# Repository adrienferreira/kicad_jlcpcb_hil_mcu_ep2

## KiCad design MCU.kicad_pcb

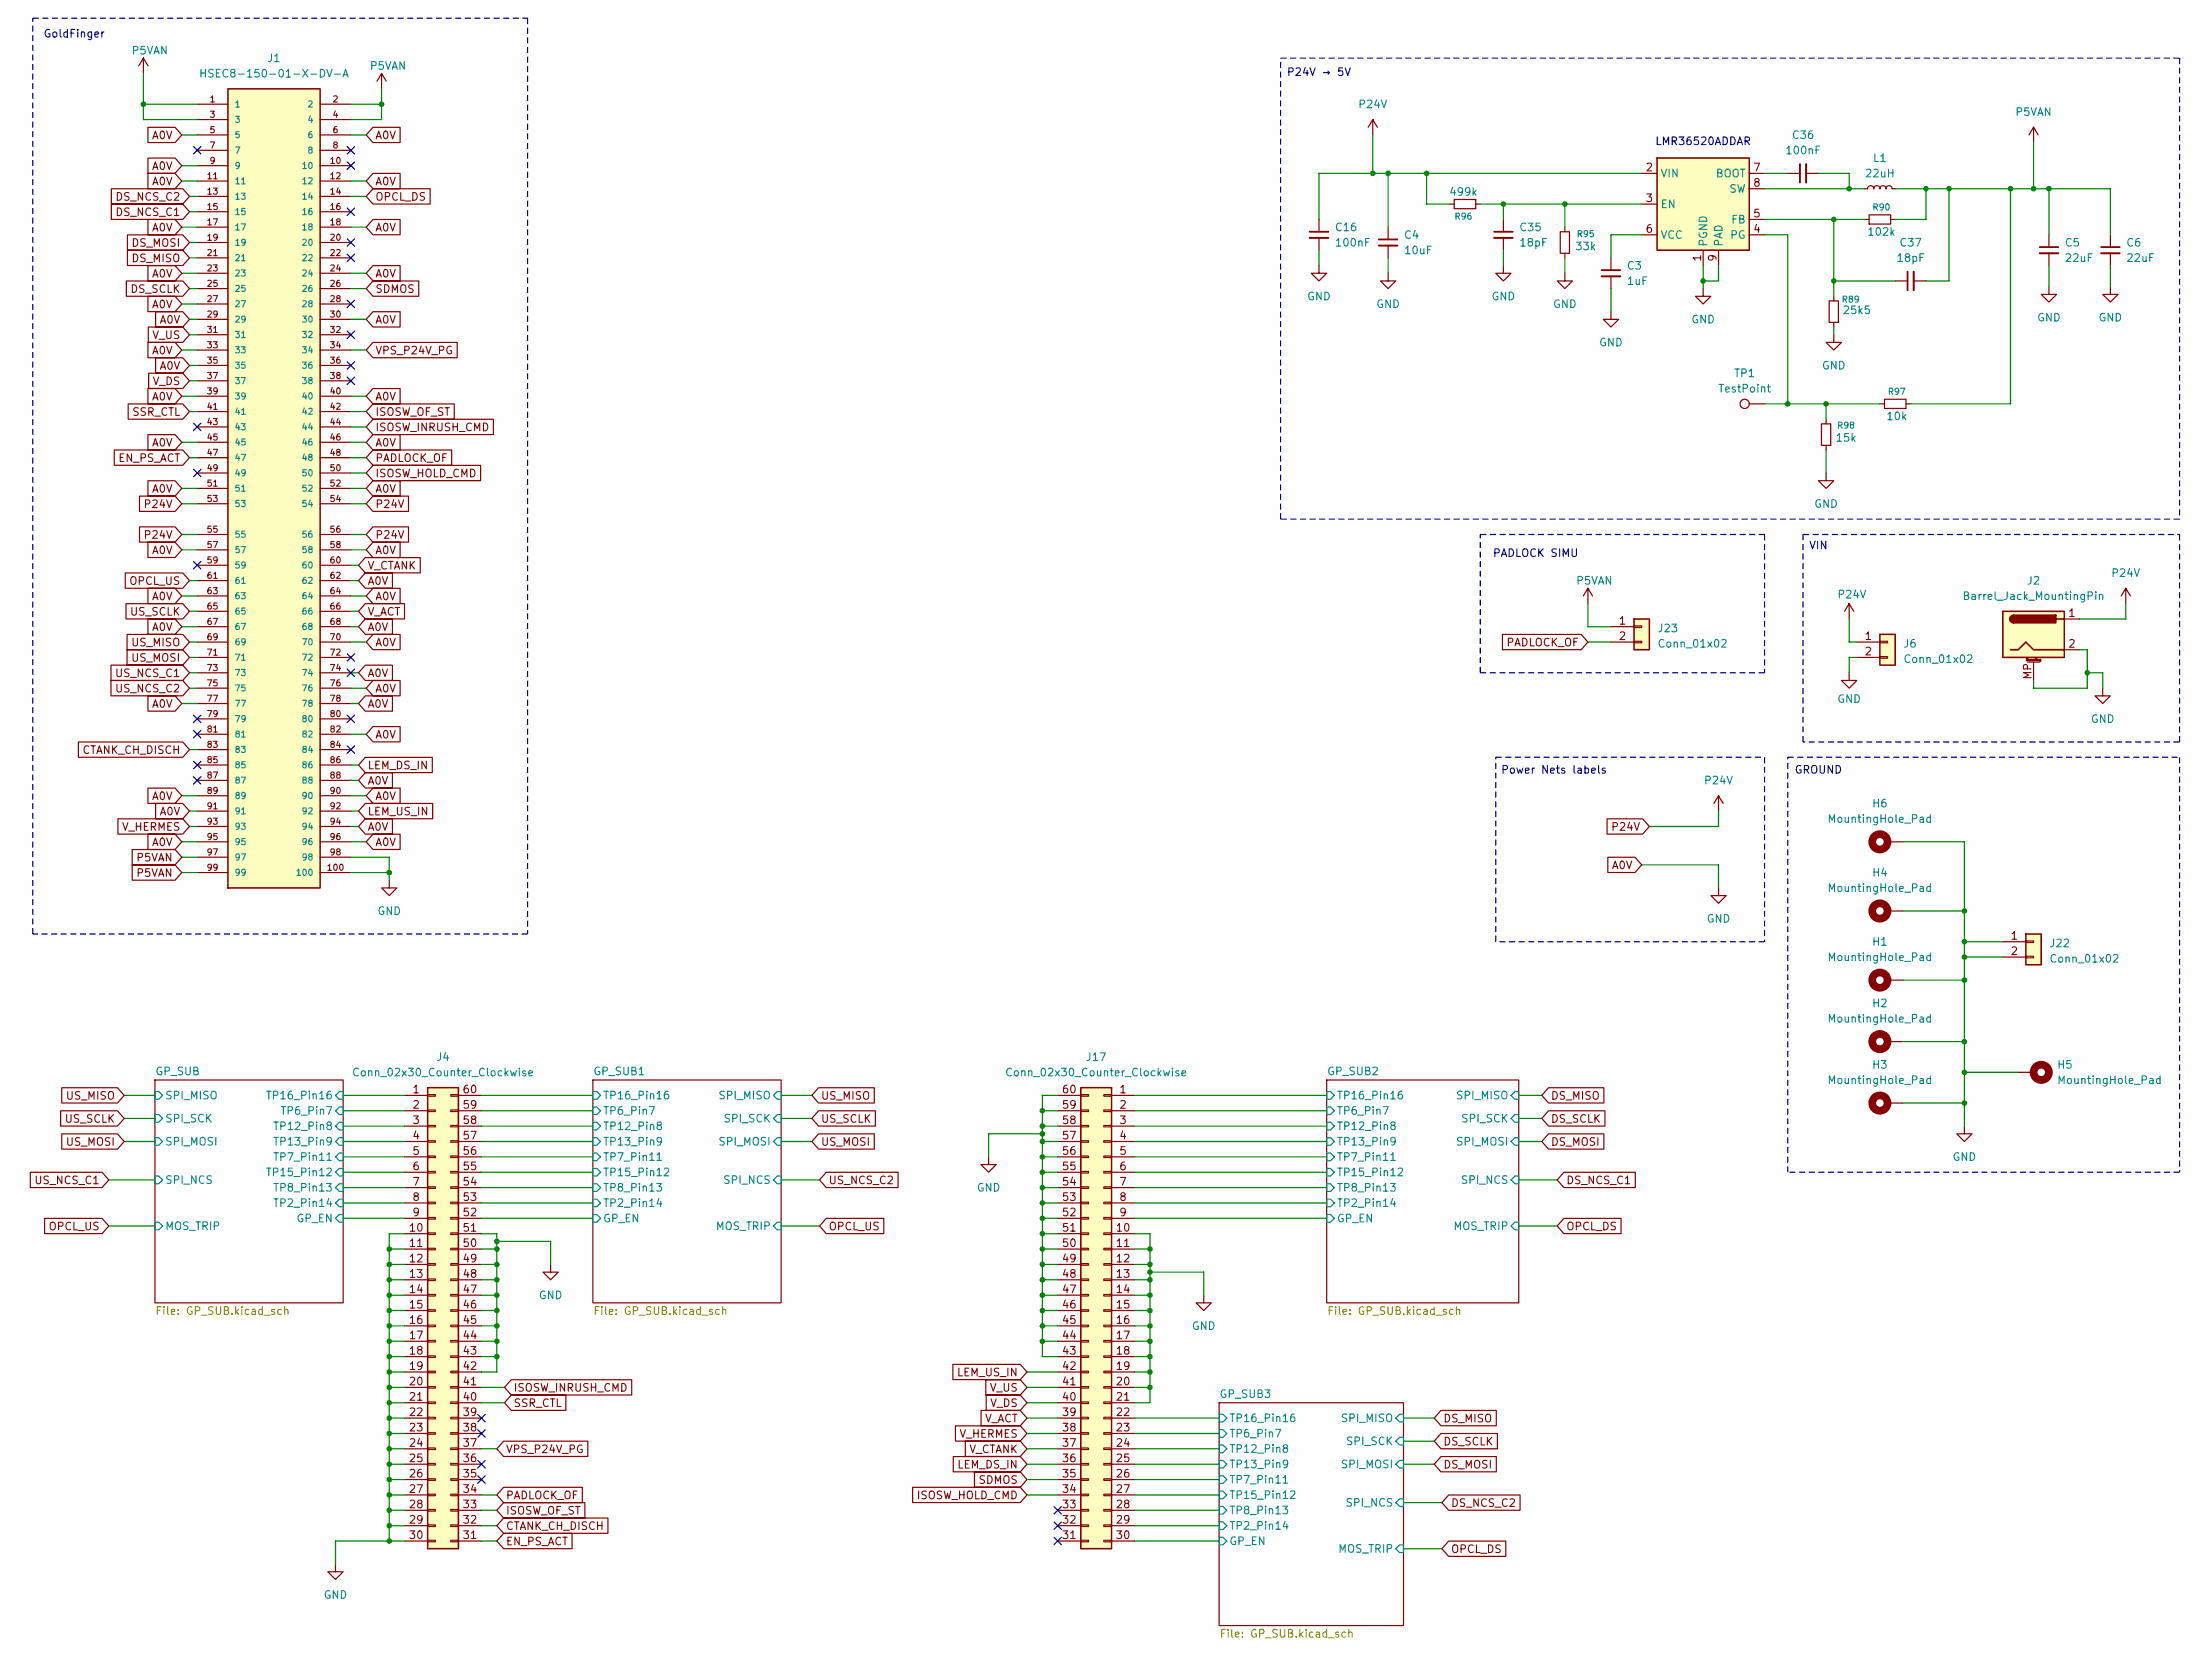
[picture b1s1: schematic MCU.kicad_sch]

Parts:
C3: 1uF; C_0603_1608Metric
C4: 10uF; C_0805_2012Metric
C5, C6: 22uF; C_0603_1608Metric
C16: 100nF; C_0603_1608Metric; JLCPCB Part# C1525
C35: 18pF; C_0402_1005Metric; JLCPCB Part # C23733
C36: 100nF; C_0603_1608Metric
C37: 18pF; C_0603_1608Metric; JLCPCB Part # C23733
H1, H2, H3, H4, H5, H6: MountingHole_Pad; MountingHole_2.2mm_M2_DIN965_Pad
J1: HSEC8-150-01-X-DV-A; Samtec_HSEC8-150-01-X-DV-A_2x50_P0.8mm_Pol27_Socket_Alignme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; PARTREV AH
J2: Barrel_Jack_MountingPin; BarrelJack_CUI_PJ-063AH_Horizontal
J4, J17: Conn_02x30_Counter_Clockwise; PinHeader_2x30_P2.54mm_Vertical
J6, J22, J23: Conn_01x02; PinHeader_1x02_P2.54mm_Vertical; JLCPCB Part# C492401
L1: 22uH; L_TDK_SLF10145
R89: 25k5; R_0603_1608Metric
R90: 102k; R_0603_1608Metric
R95: 33k; R_0603_1608Metric
R96: 499k; R_0603_1608Metric
R97: 10k; R_0603_1608Metric
R98: 15k; R_0603_1608Metric
TP1: TestPoint; TestPoint_Pad_1.5x1.5mm
U3: LMR36510ADDA; Texas_HTSOP-8-1EP_3.9x4.9mm_P1.27mm_EP2.95x4.9mm_Mask2.4x3.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

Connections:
/GP_SUB1/GP_EN: J4.52; also elsewhere on the board
/GP_SUB1/P7_VIMOSA1: J4.59; also elsewhere on the board
/GP_SUB1/P8_VIMOSA2: J4.58; also elsewhere on the board
/GP_SUB1/P9_VTMP: J4.57; also elsewhere on the board
/GP_SUB1/P11_EN_PSD: J4.56; also elsewhere on the board
/GP_SUB1/P12_GP_OPCL_T2: J4.55; also elsewhere on the board
/GP_SUB1/P13_GP_OPCL_T1: J4.54; also elsewhere on the board
/GP_SUB1/TP2_Pin14: J4.53; also elsewhere on the board
/GP_SUB1/TP16_Pin16: J4.60; also elsewhere on the board
/GP_SUB2/GP_EN: J17.9; also elsewhere on the board
/GP_SUB2/P7_VIMOSA1: J17.2; also elsewhere on the board
/GP_SUB2/P8_VIMOSA2: J17.3; also elsewhere on the board
/GP_SUB2/P9_VTMP: J17.4; also elsewhere on the board
/GP_SUB2/P11_EN_PSD: J17.5; also elsewhere on the board
/GP_SUB2/P12_GP_OPCL_T2: J17.6; also elsewhere on the board
/GP_SUB2/P13_GP_OPCL_T1: J17.7; also elsewhere on the board
/GP_SUB2/TP2_Pin14: J17.8; also elsewhere on the board
/GP_SUB2/TP16_Pin16: J17.1; also elsewhere on the board
/GP_SUB3/GP_EN: J17.30; also elsewhere on the board
/GP_SUB3/P7_VIMOSA1: J17.23; also elsewhere on the board
/GP_SUB3/P8_VIMOSA2: J17.24; also elsewhere on the board
/GP_SUB3/P9_VTMP: J17.25; also elsewhere on the board
/GP_SUB3/P11_EN_PSD: J17.26; also elsewhere on the board
/GP_SUB3/P12_GP_OPCL_T2: J17.27; also elsewhere on the board
/GP_SUB3/P13_GP_OPCL_T1: J17.28; also elsewhere on the board
/GP_SUB3/TP2_Pin14: J17.29; also elsewhere on the board
/GP_SUB3/TP16_Pin16: J17.22; also elsewhere on the board
/GP_SUB/GP_EN: J4.9; also elsewhere on the board
/GP_SUB/P7_VIMOSA1: J4.2; also elsewhere on the board
/GP_SUB/P8_VIMOSA2: J4.3; also elsewhere on the board
/GP_SUB/P9_VTMP: J4.4; also elsewhere on the board
/GP_SUB/P11_EN_PSD: J4.5; also elsewhere on the board
/GP_SUB/P12_GP_OPCL_T2: J4.6; also elsewhere on the board
/GP_SUB/P13_GP_OPCL_T1: J4.7; also elsewhere on the board
/GP_SUB/TP2_Pin14: J4.8; also elsewhere on the board
/GP_SUB/TP16_Pin16: J4.1; also elsewhere on the board
A0V: C3.2, C4.2, C5.2, C6.2, C16.2, C35.2, H1.1 (1_1), H2.1 (1_1), H3.1 (1_1), H4.1 (1_1), H5.1 (1_1), H6.1 (1_1), J1.5, J1.6, J1.9, J1.11, J1.12, J1.17, J1.18, J1.23, J1.24, J1.27, J1.29, J1.30, J1.33, J1.35, J1.39, J1.40, J1.45, J1.46, J1.51, J1.52, J1.57, J1.58, J1.62, J1.63, J1.64, J1.67, J1.68, J1.70, J1.74, J1.76, J1.77, J1.78, J1.82, J1.88, J1.89, J1.90, J1.91, J1.94, J1.95, J1.96, J1.98, J1.100, J2.2, J2.MP (MountPin_MP), J4.10, J4.11, J4.12, J4.13, J4.14, J4.15, J4.16, J4.17, J4.18, J4.19, J4.20, J4.21, J4.22, J4.23, J4.24, J4.25, J4.26, J4.27, J4.28, J4.29, J4.30, J4.42, J4.43, J4.44, J4.45, J4.46, J4.47, J4.48, J4.49, J4.50, J4.51, J6.2, J17.10, J17.11, J17.12, J17.13, J17.14, J17.15, J17.16, J17.17, J17.18, J17.19, J17.20, J17.21, J17.43, J17.44, J17.45, J17.46, J17.47, J17.48, J17.49, J17.50, J17.51, J17.52, J17.53, J17.54, J17.55, J17.56, J17.57, J17.58, J17.59, J17.60, J22.1, J22.2, R89.1, R95.1, R98.1, U3.1 (PGND), U3.9 (PAD); also elsewhere on the board
CTANK_CH_DISCH: J1.83, J4.32
DS_MISO: J1.21; also elsewhere on the board
DS_MOSI: J1.19; also elsewhere on the board
DS_NCS_C1: J1.15; also elsewhere on the board
DS_NCS_C2: J1.13; also elsewhere on the board
DS_SCLK: J1.25; also elsewhere on the board
EN_PS_ACT: J1.47, J4.31
ISOSW_HOLD_CMD: J1.50, J17.34
ISOSW_INRUSH_CMD: J1.44, J4.41
ISOSW_OF_ST: J1.42, J4.33
LEM_DS_IN: J1.86, J17.36
LEM_US_IN: J1.92, J17.42
unnamed: C36.1, U3.7 (BOOT)
unnamed: C35.1, R95.2, R96.1, U3.3 (EN)
unnamed: C37.1, R89.2, R90.1, U3.5 (FB)
unnamed: R97.1, R98.2, TP1.1 (1_1), U3.4 (PG)
unnamed: C36.2, L1.1, U3.8 (SW)
unnamed: C3.1, U3.6 (VCC)
OPCL_DS: J1.14; also elsewhere on the board
OPCL_US: J1.61; also elsewhere on the board
P5VAN: C5.1, C6.1, C37.2, J1.1, J1.2, J1.3, J1.4, J1.97, J1.99, J23.1, L1.2, R90.2, R97.2; also elsewhere on the board
P24V: C4.1, C16.1, J1.53, J1.54, J1.55, J1.56, J2.1, J6.1, R96.2, U3.2 (VIN)
PADLOCK_OF: J1.48, J4.34, J23.2
SDMOS: J1.26, J17.35
SSR_CTL: J1.41, J4.40
US_MISO: J1.69; also elsewhere on the board
US_MOSI: J1.71; also elsewhere on the board
US_NCS_C1: J1.73; also elsewhere on the board
US_NCS_C2: J1.75; also elsewhere on the board
US_SCLK: J1.65; also elsewhere on the board
VPS_P24V_PG: J1.34, J4.37
V_ACT: J1.66, J17.39
V_CTANK: J1.60, J17.37
V_DS: J1.37, J17.40
V_HERMES: J1.93, J17.38
V_US: J1.31, J17.41

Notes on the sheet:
P24V → 5V
GoldFinger
Power Nets labels
GROUND
LMR36520ADDAR
PADLOCK SIMU
VIN

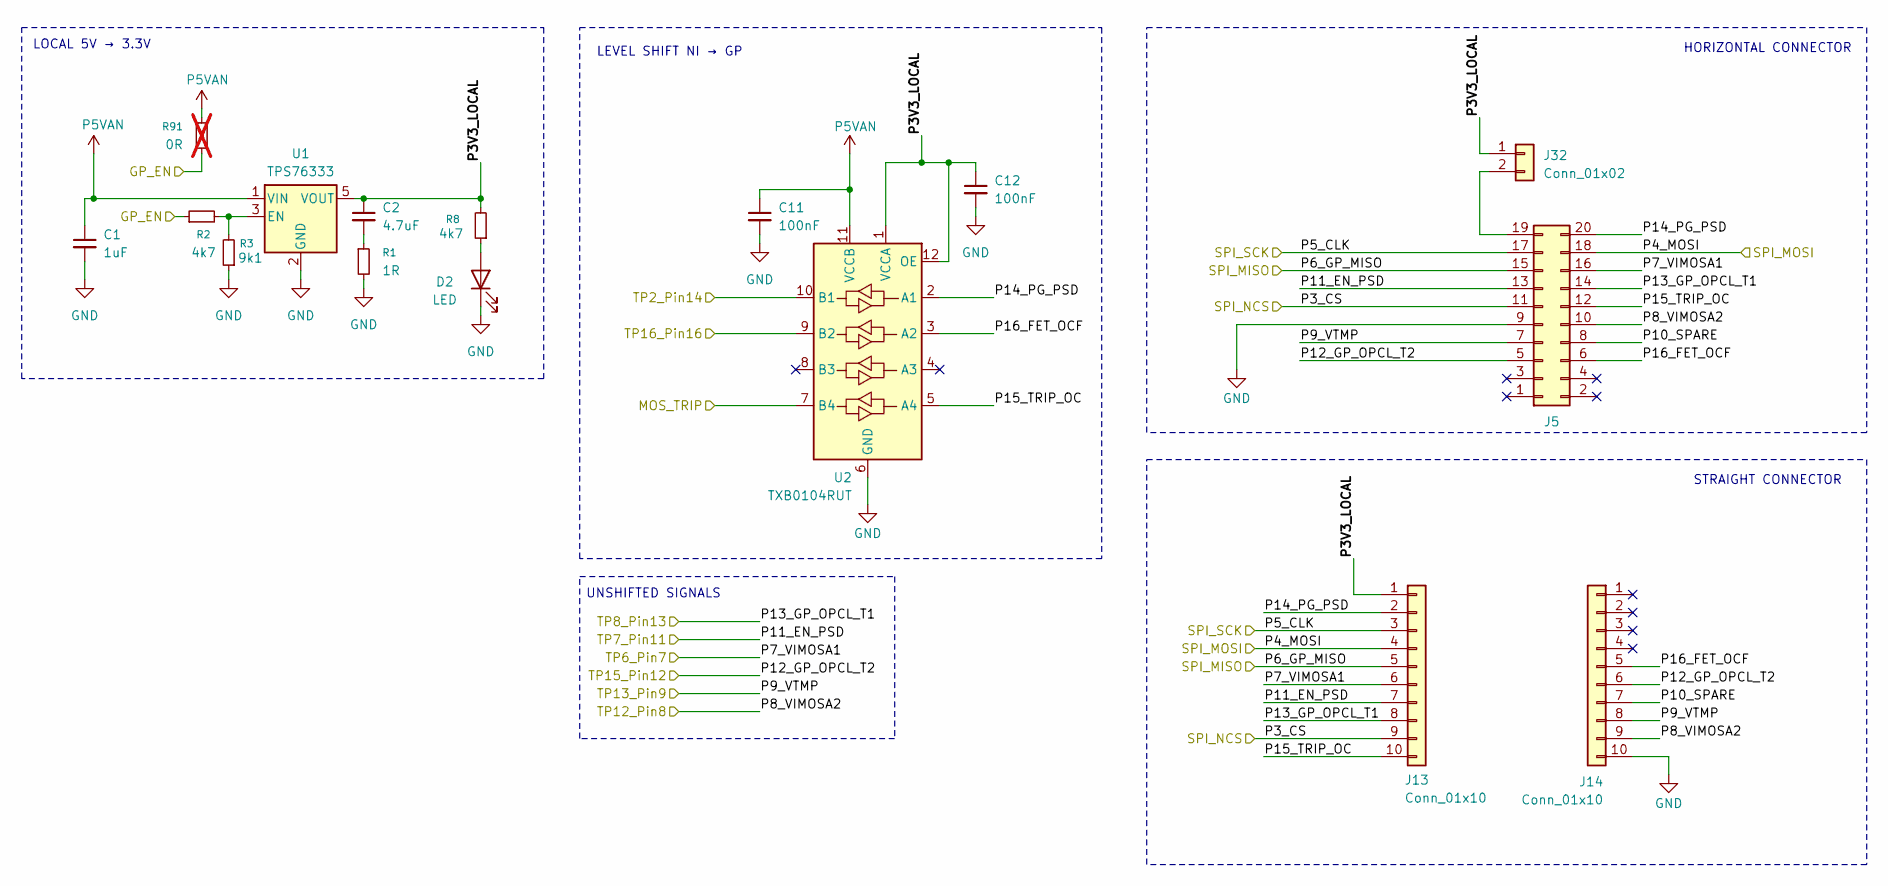
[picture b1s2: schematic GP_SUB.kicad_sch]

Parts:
C1: 1uF; C_0603_1608Metric
C2: 4.7uF; C_0603_1608Metric
C11, C12: 100nF; C_0402_1005Metric; JLCPCB Part# C1525
D2: LED; LED_0805_2012Metric; JLCPCB Part# C25170728
J5: Conn_02x10_Odd_Even; PinHeader_2x10_P2.54mm_Vertical; JLCPCB Part# C706900
J13, J14: Conn_01x10; PinSocket_1x10_P2.54mm_Vertical
J32: Conn_01x02; PinHeader_1x02_P2.54mm_Vertical; JLCPCB Part# C492401
R1: 1R; R_0603_1608Metric
R2: 4k7; R_0603_1608Metric
R3: 9k1; R_0603_1608Metric
R8: 4k7; R_0603_1608Metric; JLCPCB Part# C23138
R91: 0R; R_0603_1608Metric; not fitted
U1: TPS76333; SOT-23-5
U2: TXB0104RUT; Texas_R-PUQFN-N12

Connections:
/GP_SUB/GP_EN: R2.1, R91.2; also elsewhere on the board
/GP_SUB/P3V3_LOCAL: C2.1, C12.1, J13.1, J32.1, R8.2, U1.5 (VOUT), U2.1 (VCCA), U2.12 (OE)
/GP_SUB/P7_VIMOSA1: J5.16, J13.6; also elsewhere on the board
/GP_SUB/P8_VIMOSA2: J5.10, J14.9; also elsewhere on the board
/GP_SUB/P9_VTMP: J5.7, J14.8; also elsewhere on the board
/GP_SUB/P10_SPARE: J5.8, J14.7
/GP_SUB/P11_EN_PSD: J5.13, J13.7; also elsewhere on the board
/GP_SUB/P12_GP_OPCL_T2: J5.5, J14.6; also elsewhere on the board
/GP_SUB/P13_GP_OPCL_T1: J5.14, J13.8; also elsewhere on the board
/GP_SUB/P14_PG_PSD: J5.20, J13.2, U2.2 (A1)
/GP_SUB/P15_TRIP_OC: J5.12, J13.10, U2.5 (A4)
/GP_SUB/P16_FET_OCF: J5.6, J14.5, U2.3 (A2)
/GP_SUB/TP2_Pin14: U2.10 (B1); also elsewhere on the board
/GP_SUB/TP16_Pin16: U2.9 (B2); also elsewhere on the board
A0V: C1.2, C11.2, C12.2, D2.1 (K), J5.9, J14.10, R1.2, R3.1, U1.2 (GND), U2.6 (GND); also elsewhere on the board
unnamed: C2.2, R1.1
unnamed: D2.2 (A), R8.1
unnamed: J5.19, J32.2
unnamed: R2.2, R3.2, U1.3 (EN)
OPCL_US: U2.7 (B4); also elsewhere on the board
P5VAN: C1.1, C11.1, R91.1, U1.1 (VIN), U2.11 (VCCB); also elsewhere on the board
US_MISO: J5.15, J13.5; also elsewhere on the board
US_MOSI: J5.18, J13.4; also elsewhere on the board
US_NCS_C1: J5.11, J13.9; also elsewhere on the board
US_SCLK: J5.17, J13.3; also elsewhere on the board

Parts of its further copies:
C15, C19, C23, C25, C29, C31: 100nF; C_0402_1005Metric; JLCPCB Part# C1525
C21, C27, C33: 1uF; C_0603_1608Metric
C22, C28, C34: 4.7uF; C_0603_1608Metric
D4, D5, D6: LED; LED_0805_2012Metric; JLCPCB Part# C25170728
J7, J8, J11, J12, J18, J19: Conn_01x10; PinSocket_1x10_P2.54mm_Vertical
J9, J15, J20: Conn_01x02; PinHeader_1x02_P2.54mm_Vertical; JLCPCB Part# C492401
J10, J16, J21: Conn_02x10_Odd_Even; PinHeader_2x10_P2.54mm_Vertical; JLCPCB Part# C706900
R29, R93, R94: 0R; R_0603_1608Metric; not fitted
R30, R57, R77: 4k7; R_0603_1608Metric
R31, R58, R78: 9k1; R_0603_1608Metric
R32, R59, R79: 1R; R_0603_1608Metric
R68, R88, R92: 4k7; R_0603_1608Metric; JLCPCB Part# C23138
U6, U9, U12: TXB0104RUT; Texas_R-PUQFN-N12
U8, U11, U14: TPS76333; SOT-23-5

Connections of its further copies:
/GP_SUB1/GP_EN: R29.2, R30.1; also elsewhere on the board
/GP_SUB1/P3V3_LOCAL: C19.1, C22.1, J7.1, J9.1, R92.2, U6.1 (VCCA), U6.12 (OE), U8.5 (VOUT)
/GP_SUB1/P7_VIMOSA1: J7.6, J10.16; also elsewhere on the board
/GP_SUB1/P8_VIMOSA2: J8.9, J10.10; also elsewhere on the board
/GP_SUB1/P9_VTMP: J8.8, J10.7; also elsewhere on the board
/GP_SUB1/P10_SPARE: J8.7, J10.8
/GP_SUB1/P11_EN_PSD: J7.7, J10.13; also elsewhere on the board
/GP_SUB1/P12_GP_OPCL_T2: J8.6, J10.5; also elsewhere on the board
/GP_SUB1/P13_GP_OPCL_T1: J7.8, J10.14; also elsewhere on the board
/GP_SUB1/P14_PG_PSD: J7.2, J10.20, U6.2 (A1)
/GP_SUB1/P15_TRIP_OC: J7.10, J10.12, U6.5 (A4)
/GP_SUB1/P16_FET_OCF: J8.5, J10.6, U6.3 (A2)
/GP_SUB1/TP2_Pin14: U6.10 (B1); also elsewhere on the board
/GP_SUB1/TP16_Pin16: U6.9 (B2); also elsewhere on the board
/GP_SUB2/GP_EN: R57.1, R93.2; also elsewhere on the board
/GP_SUB2/P3V3_LOCAL: C25.1, C28.1, J11.1, J15.1, R68.2, U9.1 (VCCA), U9.12 (OE), U11.5 (VOUT)
/GP_SUB2/P7_VIMOSA1: J11.6, J16.16; also elsewhere on the board
/GP_SUB2/P8_VIMOSA2: J12.9, J16.10; also elsewhere on the board
/GP_SUB2/P9_VTMP: J12.8, J16.7; also elsewhere on the board
/GP_SUB2/P10_SPARE: J12.7, J16.8
/GP_SUB2/P11_EN_PSD: J11.7, J16.13; also elsewhere on the board
/GP_SUB2/P12_GP_OPCL_T2: J12.6, J16.5; also elsewhere on the board
/GP_SUB2/P13_GP_OPCL_T1: J11.8, J16.14; also elsewhere on the board
/GP_SUB2/P14_PG_PSD: J11.2, J16.20, U9.2 (A1)
/GP_SUB2/P15_TRIP_OC: J11.10, J16.12, U9.5 (A4)
/GP_SUB2/P16_FET_OCF: J12.5, J16.6, U9.3 (A2)
/GP_SUB2/TP2_Pin14: U9.10 (B1); also elsewhere on the board
/GP_SUB2/TP16_Pin16: U9.9 (B2); also elsewhere on the board
/GP_SUB3/GP_EN: R77.1, R94.2; also elsewhere on the board
/GP_SUB3/P3V3_LOCAL: C31.1, C34.1, J18.1, J20.1, R88.2, U12.1 (VCCA), U12.12 (OE), U14.5 (VOUT)
/GP_SUB3/P7_VIMOSA1: J18.6, J21.16; also elsewhere on the board
/GP_SUB3/P8_VIMOSA2: J19.9, J21.10; also elsewhere on the board
/GP_SUB3/P9_VTMP: J19.8, J21.7; also elsewhere on the board
/GP_SUB3/P10_SPARE: J19.7, J21.8
/GP_SUB3/P11_EN_PSD: J18.7, J21.13; also elsewhere on the board
/GP_SUB3/P12_GP_OPCL_T2: J19.6, J21.5; also elsewhere on the board
/GP_SUB3/P13_GP_OPCL_T1: J18.8, J21.14; also elsewhere on the board
/GP_SUB3/P14_PG_PSD: J18.2, J21.20, U12.2 (A1)
/GP_SUB3/P15_TRIP_OC: J18.10, J21.12, U12.5 (A4)
/GP_SUB3/P16_FET_OCF: J19.5, J21.6, U12.3 (A2)
/GP_SUB3/TP2_Pin14: U12.10 (B1); also elsewhere on the board
/GP_SUB3/TP16_Pin16: U12.9 (B2); also elsewhere on the board
A0V: C15.2, C19.2, C21.2, C23.2, C25.2, C27.2, C29.2, C31.2, C33.2, D4.1 (K), D5.1 (K), D6.1 (K), J8.10, J10.9, J12.10, J16.9, J19.10, J21.9, R31.1, R32.2, R58.1, R59.2, R78.1, R79.2, U6.6 (GND), U8.2 (GND), U9.6 (GND), U11.2 (GND), U12.6 (GND), U14.2 (GND); also elsewhere on the board
DS_MISO: J11.5, J16.15, J18.5, J21.15; also elsewhere on the board
DS_MOSI: J11.4, J16.18, J18.4, J21.18; also elsewhere on the board
DS_NCS_C1: J11.9, J16.11; also elsewhere on the board
DS_NCS_C2: J18.9, J21.11; also elsewhere on the board
DS_SCLK: J11.3, J16.17, J18.3, J21.17; also elsewhere on the board
unnamed: C22.2, R32.1
unnamed: C28.2, R59.1
unnamed: C34.2, R79.1
unnamed: D4.2 (A), R92.1
unnamed: D5.2 (A), R68.1
unnamed: D6.2 (A), R88.1
unnamed: J9.2, J10.19
unnamed: J15.2, J16.19
unnamed: J20.2, J21.19
unnamed: R30.2, R31.2, U8.3 (EN)
unnamed: R57.2, R58.2, U11.3 (EN)
unnamed: R77.2, R78.2, U14.3 (EN)
OPCL_DS: U9.7 (B4), U12.7 (B4); also elsewhere on the board
OPCL_US: U6.7 (B4); also elsewhere on the board
P5VAN: C15.1, C21.1, C23.1, C27.1, C29.1, C33.1, R29.1, R93.1, R94.1, U6.11 (VCCB), U8.1 (VIN), U9.11 (VCCB), U11.1 (VIN), U12.11 (VCCB), U14.1 (VIN); also elsewhere on the board
US_MISO: J7.5, J10.15; also elsewhere on the board
US_MOSI: J7.4, J10.18; also elsewhere on the board
US_NCS_C2: J7.9, J10.11; also elsewhere on the board
US_SCLK: J7.3, J10.17; also elsewhere on the board

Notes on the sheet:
LOCAL 5V → 3.3V
HORIZONTAL CONNECTOR
STRAIGHT CONNECTOR
LEVEL SHIFT NI → GP
UNSHIFTED SIGNALS

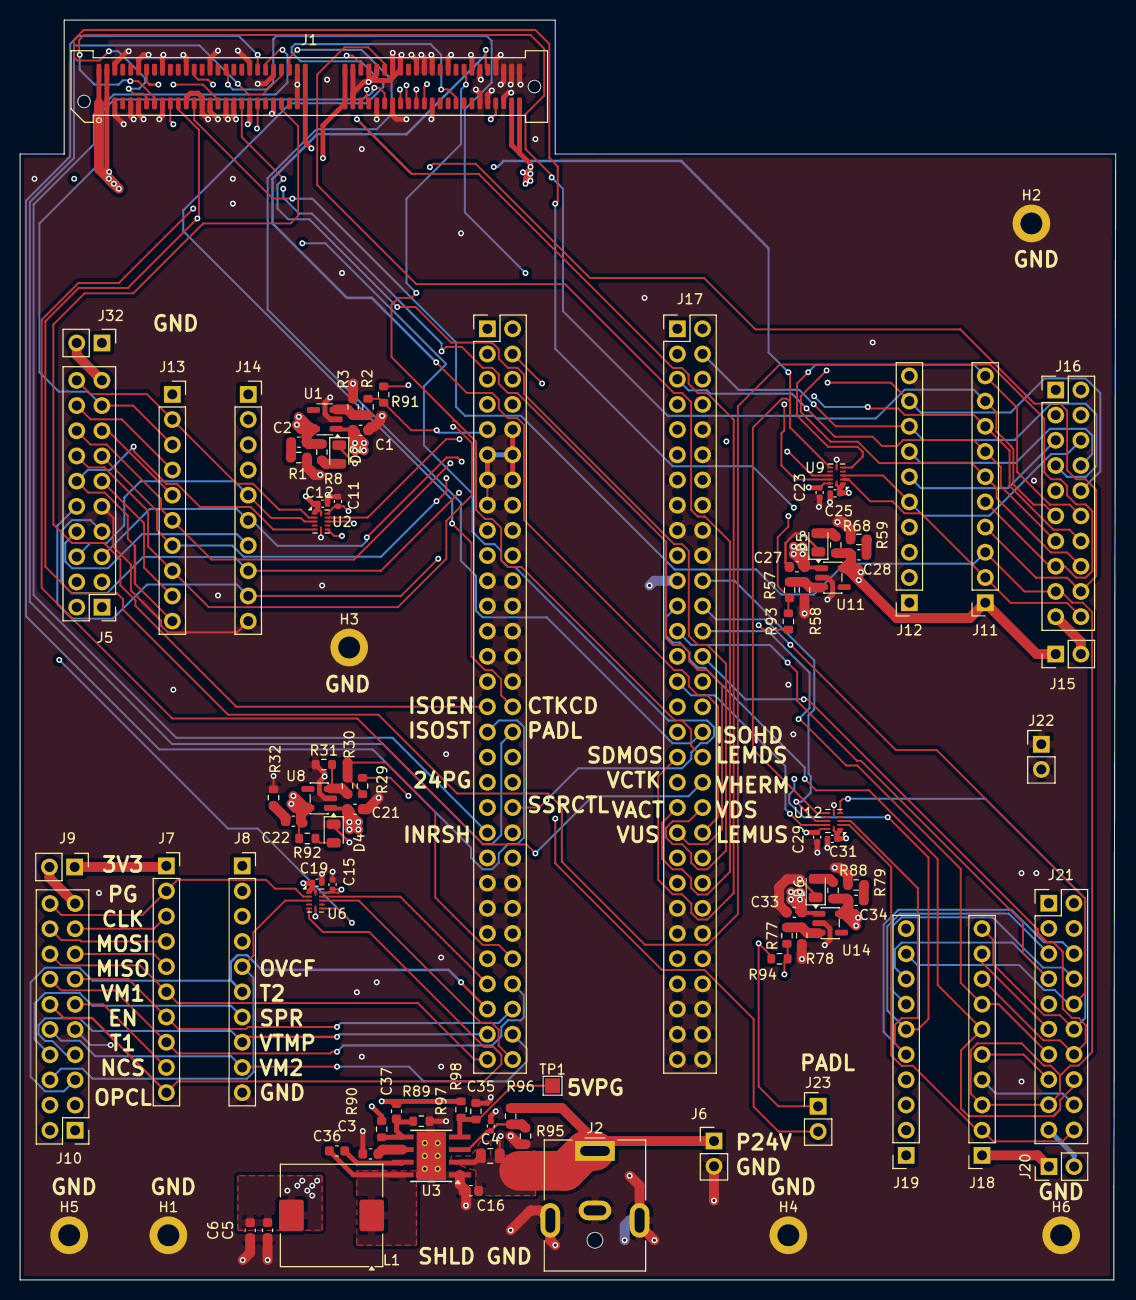
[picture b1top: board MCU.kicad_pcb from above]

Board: 4 copper layers, 110.4 x 127.0 mm, 94 parts (0 on the bottom side), 109 nets.

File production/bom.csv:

Designator,Footprint,Quantity,Value,LCSC Part #
"C1, C21, C27, C3, C33",0603,5,1uF,
"C11, C12, C15, C19, C23, C25, C29, C31",0402,8,100nF,
"C16, C36",0603,2,100nF,
"C2, C22, C28, C34",0603,4,4.7uF,
C35,0402,1,18pF,C33149
C37,0603,1,18pF,C1647
C4,0805,1,10uF,C440198
"C5, C6",0603,2,22uF,C5116073
"D2, D4, D5, D6",0805,4,LED,
J1,Samtec_HSEC8-150-01-X-DV-A_2x50_P0.8mm_Pol27_Socket_AlignmentPins,1,HSEC8-150-01-X-DV-A,C6208430
"J10, J16, J21, J5",PinHeader_2x10_P2.54mm_Vertical,4,Conn_02x10_Odd_Even,C706900
"J11, J12, J13, J14, J18, J19, J7, J8",PinSocket_1x10_P2.54mm_Vertical,8,Conn_01x10,C5116489
"J15, J20, J22, J23, J32, J6, J9",PinHeader_1x02_P2.54mm_Vertical,7,Conn_01x02,C492401
"J17, J4",PinHeader_2x30_P2.54mm_Vertical,2,Conn_02x30_Counter_Clockwise,C19190515
J2,BarrelJack_CUI_PJ-063AH_Horizontal,1,Barrel_Jack_MountingPin,C22434582
L1,L_TDK_SLF10145,1,22uH,C2041357
"R1, R32, R59, R79",0603,4,1R,
"R2, R30, R57, R68, R77, R8, R88, R92",0603,8,4k7,
"R3, R31, R58, R78",0603,4,9k1,
R89,0603,1,25k5,
R90,0603,1,102k,
R95,0603,1,33k,
R96,0603,1,499k,
R97,0603,1,10k,
R98,0603,1,15k,
"U1, U11, U14, U8",SOT-23-5,4,TPS76333,C544583
"U12, U2, U6, U9",Texas_R-PUQFN-N12,4,TXB0104RUT,C105266
U3,Texas_HTSOP-8-1EP_3.9x4.9mm_P1.27mm_EP2.95x4.9mm_Mask2.4x3.1mm_ThermalVias,1,LMR36510ADDA,C1858393
